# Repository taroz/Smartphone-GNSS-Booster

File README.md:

# Smartphone GNSS Booster

Open hardware and software for real-time centimeter-level positioning with an ordinary
Android smartphone.

The GNSS Booster mounted on a Google Pixel 7 Pro. The active antenna is connected to the
SMA input of the booster board. The board is attached to the back of the phone so that its
patch antenna faces the phone's internal GNSS antenna, and it is powered from the phone
through a wireless charging coil.

## Signal quality with and without the booster

https://github.com/user-attachments/assets/fdf9c746-18d8-440e-81c1-8e80b914b0a0

C/N0 of the signals tracked by the phone's built-in receiver, shown in GnssLogger, without
and with the booster.

## Real-time RTK while walking

https://github.com/user-attachments/assets/c614222c-13b6-4745-9687-ba6e5637af83

The RTCM Streamer app streams observations to the cloud RTK server while walking and
displays the returned centimeter-level RTK solution (`FIX`) in real time.

## How it works

Smartphones use small, linearly polarized GNSS antennas. The resulting raw measurements are
so noisy that RTK cannot reliably resolve the carrier-phase integer ambiguities. This project
addresses the problem from two sides:

1. **gnss-booster** – a small board mounted on the phone. It takes the signal from an
   external active GNSS antenna and re-radiates it into the phone's internal antenna
   through an L1/L5 patch antenna. This greatly improves the signal strength and the
   measurement quality of the phone's built-in GNSS receiver.
2. **android-rtcm-streamer** – an Android app that reads the phone's raw GNSS
   measurements, converts them to RTCM3 MSM observations and streams them to an RTK
   server. The server's position solution is streamed back and displayed on the phone.

A cloud RTK server running `rtkrcv` from [rtklibexplorer's RTKLIB](https://github.com/rtklibexplorer/RTKLIB)
completes the system. The server is not part of this repository; the app's README shows the
`rtkrcv` configuration it expects.

## System overview

(1) The GNSS Booster receives the satellite signals with an external active antenna and
re-radiates them into the phone. (2) The RTCM Streamer app reads the raw measurements,
converts them to RTCM observations and sends them to (3) a cloud RTK server, which returns
the RTK solution to the phone.

## Contents

| Directory | What it is |
|---|---|
| [`gnss-booster/`](gnss-booster/) | KiCad 10 project of the re-radiator board: schematic, layout, project libraries, Gerbers, BOM with LCSC part numbers, placement files |
| [`android-rtcm-streamer/`](android-rtcm-streamer/) | Android app (Kotlin + RTKLIB via JNI): raw measurements to RTCM3 MSM7, TCP uplink/downlink, RINEX and GnssLogger-compatible logging |

Each directory has its own README with build, fabrication and usage instructions.

## Status

- Tested with a Google Pixel 7 Pro (Android 16).
- The board re-radiates GNSS signals. Depending on your country, operating a GNSS
  re-radiator may require a license or may be restricted to shielded environments.
  Check your local radio regulations before use.

## License

- **Hardware** ([`gnss-booster/`](gnss-booster/)): CERN Open Hardware Licence Version 2 -
  Permissive (CERN-OHL-P-2.0), see [`gnss-booster/LICENSE`](gnss-booster/LICENSE).
- **Software** ([`android-rtcm-streamer/`](android-rtcm-streamer/)) and everything else in
  this repository: MIT License, see [`LICENSE`](LICENSE). The app bundles parts of
  [RTKLIB](https://github.com/rtklibexplorer/RTKLIB) (BSD 2-Clause), see
  [`android-rtcm-streamer/app/src/main/cpp/rtklib/LICENSE.txt`](android-rtcm-streamer/app/src/main/cpp/rtklib/LICENSE.txt).

## Publications

If you use this project in your research, please cite one of the following papers.

- Taro Suzuki, "Smartphone GNSS Booster: Centimeter-Level Pedestrian Positioning Using a
  Portable Signal Re-Radiator," *Proceedings of the ION 2026 Pacific PNT Meeting*,
  Honolulu, Hawaii, April 2026, pp. 512–524. [**Paper**](http://arxiv.org/abs/2609.23456)
- Taro Suzuki, "Smartphone GNSS Booster for Real-Time Centimeter-Level Kinematic
  Positioning: An Open Hardware and Software Approach," *Proceedings of the ION GNSS+ 2026*. [**Slides**](https://www.taroz.net/paper/IONGNSS_2026_PPT.pdf)

## Acknowledgements

[Takuho Munetomo](https://github.com/takuhoTech) contributed to the design of the GNSS
booster board.

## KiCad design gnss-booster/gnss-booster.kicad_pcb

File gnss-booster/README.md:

# GNSS Booster

Smartphone-mounted GNSS signal re-radiator, designed in [KiCad](https://www.kicad.org/) 10.

An external active GNSS antenna (Harxon HX-CU7603A or Beitian BT-230F, with its own
LNA, powered through the coax by this board) is connected to the SMA input. The board
splits the signal into L1 and L5 paths and feeds a dual-band patch antenna on the back
side, which re-radiates the signal into the smartphone's internal GNSS antenna. The
phone therefore receives a much cleaner signal than it would with its own antenna alone,
which is what makes RTK with the [android-rtcm-streamer](../android-rtcm-streamer) app
practical.

Off-the-shelf parts used together with the board:

- **Active antenna** – Harxon HX-CU7603A or Beitian BT-230F, connected to the SMA
  input `J1`.
- **Power** – a commercial Qi wireless charging receiver
  ([Nillkin Magic Tag](https://www.amazon.com/Nillkin-Wireless-Charging-Receiver-Charger/dp/B01M11UT3V/)).
  Its 5 V output is wired to `J2` and powers the board and, through the bias tee, the
  active antenna's LNA.

| Top (components) | Bottom (patch antenna) |
|---|---|
|  |  |

- Schematic: [docs/gnss-booster-schematic.pdf](docs/gnss-booster-schematic.pdf)
- Layout overview: [docs/gnss-booster-layout.svg](docs/gnss-booster-layout.svg)

## Circuit

Signal path, from the SMA input `J1` to the patch antenna `AE1`:

1. **Bias tee** – the inductor `L1` (120 nH) injects +5 V from `J2` onto the coax to
   power the external antenna's LNA; `C1` (47 pF) blocks the DC from the RF path.
   `C2`/`C3`/`C4` decouple the supply.
2. **Attenuator** – `R3`/`R4`/`R5` (37 Ω series, 150 Ω shunts) form a ~6 dB π attenuator
   that sets the re-radiated level and improves the match seen by the divider.
3. **Power divider** – `U2` (TTM Xinger PD0922J5050S2HF, 0.95–2.15 GHz Wilkinson)
   splits the signal into an L1 and an L5 branch. `R2` (100 Ω) is the divider's
   isolation resistor.
4. **L1 branch** – `U1` (TTM Xinger X3C14P1-03S, 1.2–1.7 GHz 3 dB 90° hybrid) drives the
   two orthogonal L1 feed points of the patch in quadrature to produce circular
   polarization. `R1` (50 Ω) terminates the hybrid's isolated port.
5. **L5 branch** – connected directly to the patch's L5 feed point.
6. **ESD protection** – `D1`–`D4` (Littelfuse AXGD10402KR) on the SMA input and on each
   antenna feed.

The patch antenna (Taoglas HP5354.A, 35 × 35 mm, L1 + L5) is mounted on the bottom
side, so the top side with the components faces away from the phone.

## Board

| Item | Value |
|---|---|
| Size | 50 × 57.5 mm (50 × 50 mm body plus the SMA tab) |
| Layers | 2 (F.Cu / B.Cu), FR-4 core 0.71 mm, total 0.8 mm |
| Surface finish | ENIG |
| Min. track / clearance | 0.1 mm / 0.1 mm |
| Min. via | 0.41 mm diameter, 0.2 mm drill |

Fabrication and assembly files exported for JLCPCB with the *Fabrication Toolkit*
plugin are in [`production/`](production/):

- `gnss-booster.zip` – Gerbers and drill files
- `bom.csv` – BOM with LCSC part numbers (the `R4`/`R5` 150 Ω 0402 resistors have no
  LCSC number; any 1 % 0402 part works)
- `positions.csv` – component placement (CPL)
- `netlist.ipc` – IPC-D-356 netlist
- `designators.csv` – reference designators

## Bill of materials

| Ref | Part | Package | Function | LCSC |
|---|---|---|---|---|
| AE1 | Taoglas HP5354.A | 35 × 35 mm patch | L1/L5 re-radiating patch antenna (bottom side) | C30042276 |
| U1 | TTM Xinger X3C14P1-03S-1 | 6.35 × 5.08 mm | 3 dB 90° hybrid coupler, L1 quadrature feed | C36369905 |
| U2 | TTM Xinger PD0922J5050S2HF | 0805 (6-pad) | Wilkinson power divider, L1/L5 split | C5136968 |
| R1 | Vishay FCHP0402E50R0BGT1, 50 Ω | 0402 | Hybrid isolated-port termination | C4267592 |
| R2 | Vishay FC0603E1000BTBST1, 100 Ω | 0603 | Divider isolation resistor | C2076508 |
| R3 | 37 Ω | 0402 | π attenuator, series | C17168 |
| R4, R5 | 150 Ω | 0402 | π attenuator, shunt | – |
| C1 | Murata GJM1555C1H470FB01D, 47 pF | 0402 | DC block | C882562 |
| C2 | 0.1 µF | 0603 | Supply decoupling | C14663 |
| C3 | 1 µF | 0603 | Supply decoupling | C15849 |
| C4 | 10 µF | 0805 | Supply decoupling | C440198 |
| L1 | Murata LQW18ANR12G80D, 120 nH | 0603 | Bias-tee inductor | C307612 |
| D1–D4 | Littelfuse AXGD10402KR | 0402 | ESD protection | C434715 |
| J1 | Molex 73251-2440 | SMA female, edge mount | RF input from the external antenna | C588468 |
| J2 | JST SM02B-SRSS-TB | SH 1.0 mm, 2 pin | +5 V power input | C160402 |

## Opening the project

Open `gnss-booster.kicad_pro` in KiCad 10 (or newer). The project is self-contained:

- Symbols and footprints that are not in the KiCad standard library (antenna, coupler,
  divider, SMA connector, and the specific passive footprints) live in
  [`libs/gnss-booster.kicad_sym`](libs/gnss-booster.kicad_sym) and
  [`libs/gnss-booster.pretty`](libs/gnss-booster.pretty), referenced through the
  project-local `sym-lib-table` / `fp-lib-table` as library `gnss-booster`.
- Everything else comes from the standard libraries shipped with KiCad.
- 3D models for the project-library parts live under `libs/3d/`. STEP files are
  included for the Xinger power divider and the Vishay 0603 resistor; the models for the
  patch antenna, the hybrid coupler and the SMA connector are vendor files that are not
  redistributed here. Missing models only affect the 3D viewer.

## Regulatory note

This board re-radiates GNSS signals. Depending on your country, operating a GNSS
re-radiator may require a license or may be restricted to shielded environments.
Check your local radio regulations before use.

## License

Copyright (c) 2026 Taro Suzuki.

This hardware design (schematic, layout, libraries, fabrication outputs and this
documentation) is licensed under the CERN Open Hardware Licence Version 2 - Permissive
(CERN-OHL-P-2.0). You may redistribute and modify it under the terms of that licence,
see [`LICENSE`](LICENSE) or <https://ohwr.org/cern_ohl_p_v2.txt>. It is distributed
WITHOUT ANY EXPRESS OR IMPLIED WARRANTY, including of merchantability, satisfactory
quality and fitness for a particular purpose.

The Android app in [`android-rtcm-streamer/`](../android-rtcm-streamer) is licensed
separately under the MIT License (see the repository root [`LICENSE`](../LICENSE)).
Component datasheets and 3D models are the property of their respective manufacturers.

## Acknowledgements

[Takuho Munetomo](https://github.com/takuhoTech) contributed to the design of this board.

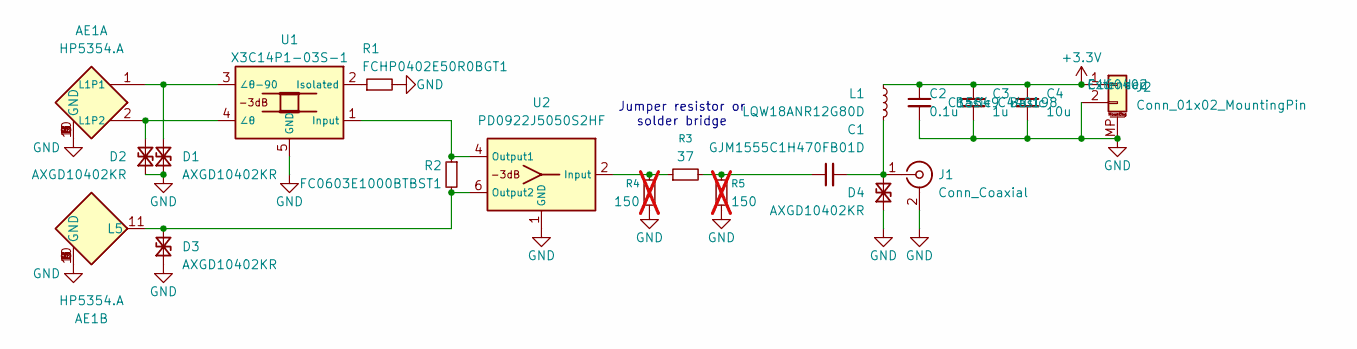
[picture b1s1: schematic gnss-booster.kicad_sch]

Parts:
AE1: HP5354.A; Taoglas_HP5354.A_GNSS
C1: GJM1555C1H470FB01D; C_Murata_xxx15_0402_1005Metric_1.0x0.5mm; LCSC C882562
C2: 0.1u; C_0603_1608Metric; LCSC C14663
C3: 1u; C_0603_1608Metric; LCSC C15849
C4: 10u; C_0805_2012Metric; LCSC C440198
D1, D2, D3, D4: AXGD10402KR; D_Littelfuse_AXGD10402KR_0402_1005Metric_1.02x0.51mm; LCSC C434715
J1: Conn_Coaxial; SMA_Molex_732512440_Female_Embed; LCSC C588468
J2: Conn_01x02_MountingPin; JST_SH_SM02B-SRSS-TB_1x02-1MP_P1.00mm_Horizontal; LCSC C160402
L1: LQW18ANR12G80D; L_Murata_LQW18ANxxxx80x_0603_1608Metric_1.65x0.99mm; LCSC C307612
R1: FCHP0402E50R0BGT1; R_0402_1005Metric; LCSC C4267592
R2: FC0603E1000BTBST1; R_Vishay_FC0603xxxxxxTxx_0603_1608Metric_1.626x0.813mm; LCSC C2076508
R3: 37; R_0402_1005Metric; LCSC C17168
R4, R5: 150; R_0402_1005Metric; not fitted
U1: X3C14P1-03S-1; RF_HybridCoupler_TTM_X3C14P1-03S; LCSC C36369905
U2: PD0922J5050S2HF; Xinger_0805_2012Metric-6_Pad0.33x0.41mm; LCSC C5136968

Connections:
+3.3V: C2.1, C3.1, C4.1, J2.1, L1.1
GND: AE1.3 (GND), AE1.4 (GND), AE1.5 (GND), AE1.6 (GND), AE1.7 (GND), AE1.8 (GND), AE1.9 (GND), AE1.10 (GND), C2.2, C3.2, C4.2, D1.1 (A1), D2.1 (A1), D3.1 (A1), D4.1 (A1), J1.2 (Ext), J2.2, J2.MP (MountPin), R1.2, R4.2, R5.2, U1.5 (GND), U2.1 (GND), U2.3 (GND), U2.5 (GND)
unnamed: AE1.1 (L1P1), D1.2 (A2), U1.3 (∠θ-90)
unnamed: AE1.2 (L1P2), D2.2 (A2), U1.4 (∠θ)
unnamed: AE1.11 (L5), D3.2 (A2), R2.2, U2.6 (Output2)
unnamed: C1.1, R3.2, R5.1
unnamed: C1.2, D4.2 (A2), J1.1 (In), L1.2
unnamed: R2.1, U1.1 (Input), U2.4 (Output1)
unnamed: R1.1, U1.2 (Isolated)
unnamed: R3.1, R4.1, U2.2 (Input)

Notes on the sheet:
Jumper resistor or solder bridge

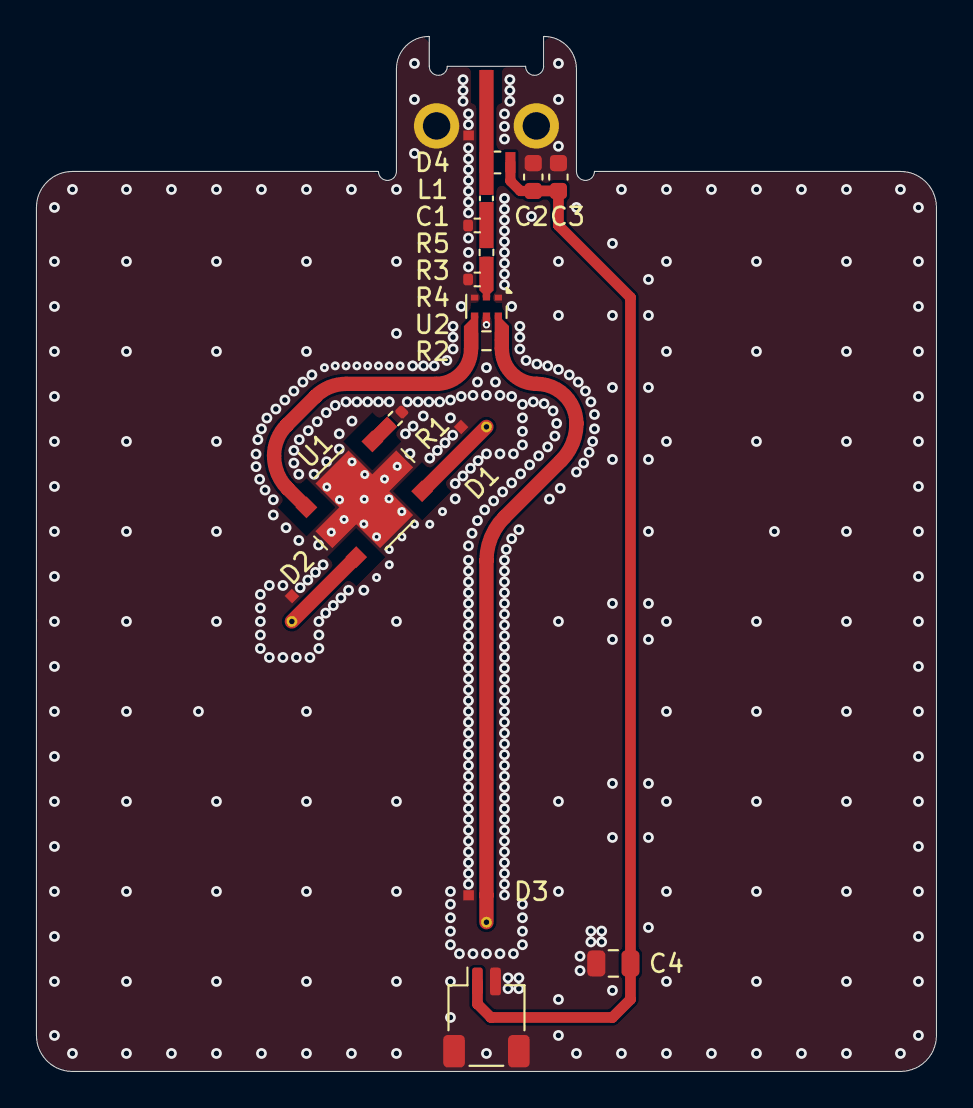
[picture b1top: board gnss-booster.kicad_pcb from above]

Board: 2 copper layers, 50.0 x 57.5 mm, 19 parts (1 on the bottom side), 10 nets.

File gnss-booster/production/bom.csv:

Designator,Footprint,Quantity,Value,LCSC Part #
AE1,Taoglas_HP5354.A_GNSS,1,HP5354.A,C30042276
C1,C_Murata_xxx15_0402_1005Metric_1.0x0.5mm,1,GJM1555C1H470FB01D,C882562
C2,0603,1,0.1u,C14663
C3,0603,1,1u,C15849
C4,0805,1,10u,C440198
"D1, D2, D3, D4",D_Littelfuse_AXGD10402KR_0402_1005Metric_1.02x0.51mm,4,AXGD10402KR,C434715
J1,SMA_Molex_732512440_Female_Embed,1,Conn_Coaxial,C588468
J2,JST_SH_SM02B-SRSS-TB_1x02-1MP_P1.00mm_Horizontal,1,Conn_01x02_MountingPin,C160402
L1,L_Murata_LQW18ANxxxx80x_0603_1608Metric_1.65x0.99mm,1,LQW18ANR12G80D,C307612
R1,0402,1,FCHP0402E50R0BGT1,C4267592
R2,R_Vishay_FC0603xxxxxxTxx_0603_1608Metric_1.626x0.813mm,1,FC0603E1000BTBST1,C2076508
R3,0402,1,37,C17168
"R4, R5",0402,2,150,
U1,RF_HybridCoupler_TTM_X3C14P1-03S,1,X3C14P1-03S-1,C36369905
U2,Xinger_0805_2012Metric-6_Pad0.33x0.41mm,1,PD0922J5050S2HF,C5136968
